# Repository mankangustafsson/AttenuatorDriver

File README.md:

# AttenuatorDriver
Attenuator switch and relay driver similar to HP11713A/B. This project covers many firsts for me: First project using KiCad, first project published on github, first Python code (GPIB control) so please bear with me.

## Hardware
The HW design started out with the solenoid control of the attenuator switches inspired by the HP 33311 product overview pdf. After a while I decided to not care about the TTL output part and just trust the LED indicators.

Each attenuator solenoid is controlled by two ULN2803 outputs. 8 attenuators in total thus requires all outputs in two ULN2803:s.

To control coaxial relays I wanted to be able to handle latching relays that is controlled by polarity switching the coil voltage. For that task I found the SN754410 Quad Half-H Driver from Texas Instruments. There are cheaper circuits that can achieve this but this is the only one I found that could handle 28V coils.

To keep the micro controller I/O pin count as low as possible I decided to control the attenuators and relays drive circuits with plain old shift registers. So three 74HC595 gets the 24 output pin count down to just four.

I also wanted to keep my options open to which kind of display I would use, so that is why both I2C and SPI connectors are available. I ended up with an LCD1602 controlled via I2C. For input I wanted to mimic the HP 11713A so I wanted 10 push buttons so two R2R ladders handles five buttons each. But I also wanted to utilize the display and I find using rotary encoders with a push button quite powerful to navigate a simple UI.

### Power Supply
This can be improved but the current design works for me. The HW is fed with 12VDC and 24VDC to the ULN2803 controlling the first four attenuators. The second set of attenuators and the relays can also be feed directly with this 24V supply. Or they can have a lower voltage controlled by their individual LM317 voltage regulator. This mean that the first attenuator group decides the highest voltage that the other atteunators and relays can use.

To remedy this I would put one extra LM317 to control the voltage to the first attenuator group and remove the J6 and J7 jumpers. This way each attenuator group and the relay pair could have their coils voltages individually set.

### Patches
I made the faulty assumption about coaxial relays could control the LED the same way the attenuators did. They do not! So the remedy is to use two free micro controller pins (I use A1 and A2) to control the relay LED indicators. Depending on LEDs used the micro controller could probably drive them directly or you could still use Q3 and Q4 to sink the current. Regardless solution you select you need to remove R4 and R6.

## Arduino Software
First of all: Do not expect any compilation support from me. You are on your own. Arduino environment is messy when it comes to how it handles libraries used. I usually import the source code of the libraries I use into the project. However since I'm not the author of the [display library] I use you have to download it yourself. The current code also includes another library, Streaming, which I only used initially in this project so remove that include statement.

Second: Parts of the code is structured and easy to read. Some parts are not structured at all and poorly documented. I'm of the opinion that code should be written to be easy to understand by other programmers and therefore would not need much documentation. It is not currently in the "easy to understand" state and it might never be.

## GPIB Control
In order to avoid the Arduino being reset every time you connect to the serial port, you need to remove the capacitor between the CH340 DTR pin and the Arduino reset pin. Note that this will make it harder to upload new software to the Arduino. You will need to push the reset button manually at the proper moment during code upload.

I've written some Python code using PyVisa to control the attenuators and relays.

[display library]:       http://www.mathertel.de/Arduino/LiquidCrystal_PCF8574.aspx

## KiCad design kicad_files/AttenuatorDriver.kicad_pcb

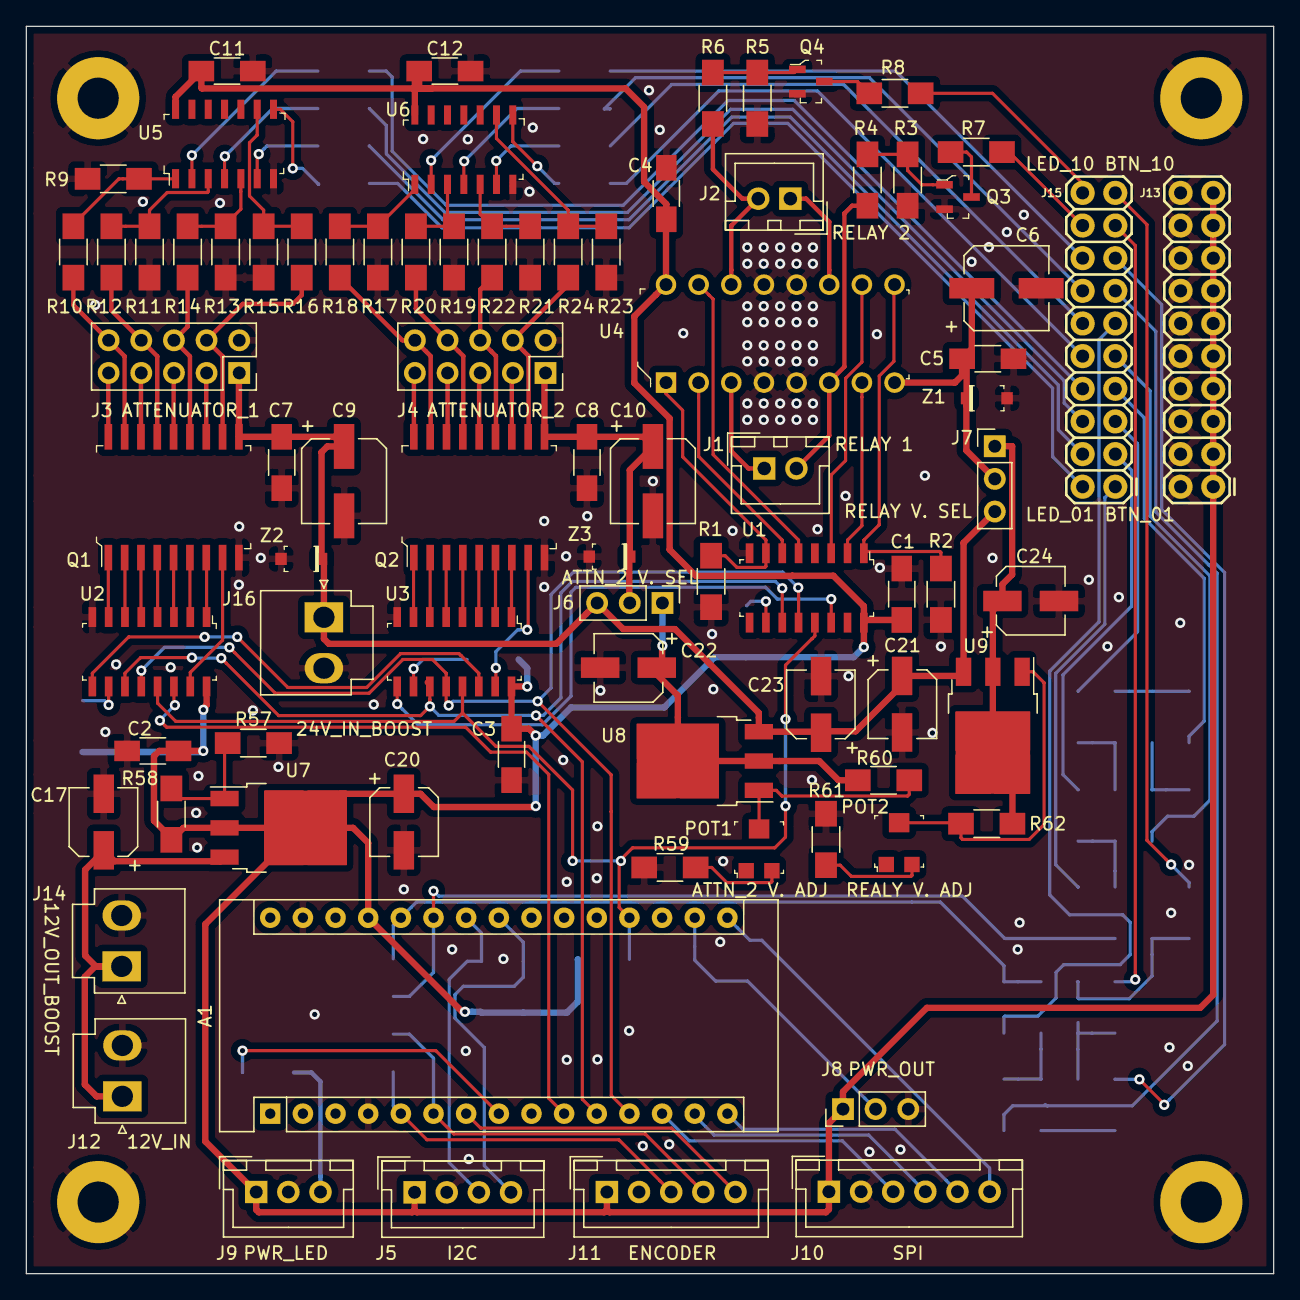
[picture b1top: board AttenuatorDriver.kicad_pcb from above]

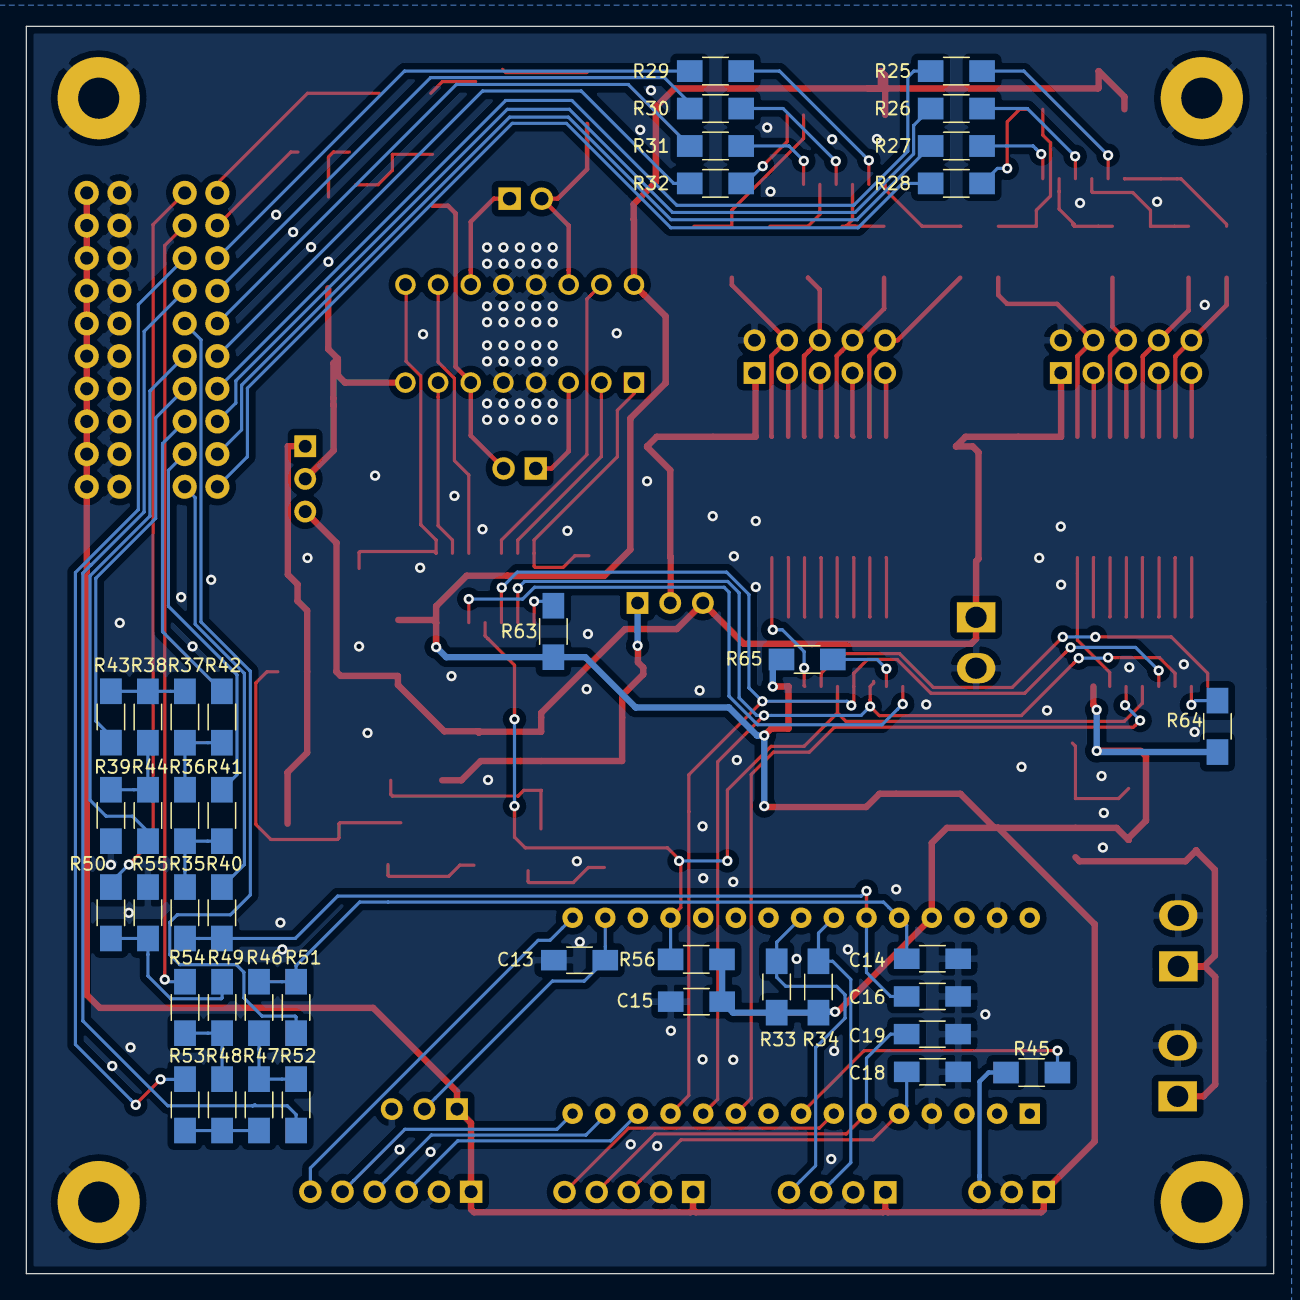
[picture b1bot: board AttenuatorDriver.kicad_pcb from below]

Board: 2 copper layers, 97.0 x 97.0 mm, 128 parts (41 on the bottom side), 126 nets.

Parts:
A1: Arduino_Nano_v3.x; Arduino_Nano
C1, C2, C3, C4, C7, C8, C11, C12, C13, C14, C15, C16, C18, C19: 0.1uF; C_1206_HandSoldering
C5: 1uF; C_1206_HandSoldering
C6, C9, C10: 47u; CP_Elec_6.3x7.7
C17, C21, C23: 1u; CP_Elec_5x5.3
C20, C22, C24: 4.7u; CP_Elec_5x5.3
H1, H2, H3, H4: MountingHole_Pad; MountingHole_3.2mm_M3_Pad
J1: RELAY_1; JST_XH_B02B-XH-A_02x2.50mm_Straight
J2: RELAY_2; JST_XH_B02B-XH-A_02x2.50mm_Straight
J3: ATTENUATOR_1; Socket_Strip_Straight_2x05_Pitch2.54mm
J4: ATTENUATOR_2; Socket_Strip_Straight_2x05_Pitch2.54mm
J5: I2C; JST_XH_B04B-XH-A_04x2.50mm_Straight
J6: DRV_PWR_SEL2; Pin_Header_Straight_1x03_Pitch2.54mm
J7: DRV_PWR_SEL3; Pin_Header_Straight_1x03_Pitch2.54mm
J8: PWR_OUT; Pin_Header_Straight_1x03_Pitch2.54mm
J9: PWR_LED; JST_XH_B03B-XH-A_03x2.50mm_Straight
J10: SPI; JST_XH_B06B-XH-A_06x2.50mm_Straight
J11: ENCODER; JST_XH_B05B-XH-A_05x2.50mm_Straight
J12: 12V_IN; JST_VH_B2P-VH-B_2x3.96mm_Vertical
J13, J15: Conn_02x10_Odd_Even; 2X10
J14: 12V_OUT_BOOST; JST_VH_B2P-VH-B_2x3.96mm_Vertical
J16: 24V_IN_BOOST; JST_VH_B2P-VH-B_2x3.96mm_Vertical
POT1, POT2: 5k; Trimpot_3.8mmx3.6mm_TC33X-2-103E
Q1, Q2: ULN2803ADWR; SOIC-18_W7.5mm
Q3, Q4: PDTC114Y; SOT-23-3
R1, R2, R4, R6, R10, R12, R14, R16, R18, R20, R22, R24, R63, R64, R65: 4.7k; R_1206_HandSoldering
R3, R5, R9, R11, R13, R15, R17, R19, R21, R23: 620; R_1206_HandSoldering
R7, R8, R25, R26, R27, R28, R29, R30, R31, R32, R58: 330; R_1206_HandSoldering
R33, R34, R56: 10k; R_1206_HandSoldering
R35, R36, R37, R38, R45, R46, R47, R48, R49, R57: 1k; R_1206_HandSoldering
R39, R40, R41, R42, R43, R44, R50, R51, R52, R53, R54, R55: 2k; R_1206_HandSoldering
R59, R61: 680; R_1206_HandSoldering
R60, R62: 240; R_1206_HandSoldering
U1, U2, U3: 74HC595; SOIC-16_W3.90mm
U4: SN754410NE; DIP-16_W7.62mm
U5, U6: SN74LS06DR; SOIC-14_W3.9mm
U7, U8, U9: V_REG_317DPACK; TO-252-3_TabPin2
Z1, Z2, Z3: MMSZ4713-TP; SOD-123

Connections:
+5V: A1.27, C1.1, C2.1, C3.1, C4.1, C11.1, C12.1, C15.2, C20.1, J5.1, J8.1, J9.1, J10.1, J11.1, J13.1, J13.3, J13.5, J13.7, J13.9, J13.11, J13.13, J13.15, J13.17, J13.19, R33.1, R34.1, R56.1, R58.1, R63.1, R64.1, R65.1, U1.16, U2.16, U3.16, U4.16, U5.14, U6.14, U7.2
+8V: C5.1, C6.1, J7.2, U4.8, Z1.K
+9V: C24.1, J7.1, R62.1, U9.2
+12V: C17.1, J12.1, J14.1, U7.3
+15V: C22.1, J6.1, R60.1, U8.2
+24V: C7.1, C9.1, C21.1, C23.1, J3.1, J6.3, J7.3, J16.1, Q1.10, U8.3, U9.3, Z2.K
+VSW: C8.1, C10.1, J4.1, J6.2, Q2.10, Z3.K
/RELAY_1A: U1.6, U4.2
/RELAY_1B: U1.2, U4.7
/RELAY_1_EN: R1.1, U1.7, U4.1
/RELAY_2A: U1.3, U4.10
/RELAY_2B: U1.5, U4.15
/RELAY_2_EN: R2.1, U1.1, U4.9
/SER_CASC_1: U2.9, U3.14
/SER_CASC_2: U1.14, U3.9
BTN_01: J15.1, R40.1
BTN_02: J15.3, R41.1
BTN_03: J15.5, R42.1
BTN_04: J15.7, R43.1
BTN_05: J15.9, R44.1
BTN_06: J15.11, R51.1
BTN_07: J15.13, R52.1
BTN_08: J15.15, R53.1
BTN_09: J15.17, R54.1
BTN_10: J15.19, R55.1
BTN_G1: A1.25, C16.2, R35.1, R40.2
BTN_G2: A1.26, C14.2, R46.1, R51.2
CE_DISP: A1.13, J10.3
ENC_BTN: A1.7, J11.5
ENC_CLK: A1.6, C19.2, J11.4
ENC_DATA: A1.5, C18.2, J11.3
GND: A1.4, A1.29, C1.2, C2.2, C3.2, C4.2, C5.2, C6.2, C7.2, C8.2, C9.2, C10.2, C11.2, C12.2, C13.1, C14.1, C15.1, C16.1, C17.2, C18.1, C19.1, C20.2, C21.2, C22.2, C23.2, C24.2, H1.1, H2.1, H3.1, H4.1, J3.2, J4.2, J5.2, J8.3, J9.2, J10.2, J11.2, J12.2, J13.2, J13.4, J13.6, J13.8, J13.10, J13.12, J13.14, J13.16, J13.18, J13.20, J14.2, J16.2, Q1.9, Q2.9, Q3.2, Q4.2, R1.2, R2.2, R3.2, R5.2, R9.2, R11.2, R13.2, R15.2, R17.2, R19.2, R21.2, R23.2, R39.2, R50.2, R57.2, R59.2, R61.2, U1.8, U2.8, U3.8, U4.4, U4.5, U4.12, U4.13, U5.7, U6.7, Z1.A, Z2.A, Z3.A
I2C_SCL: A1.24, J5.3, R34.2
I2C_SDA: A1.23, J5.4, R33.2
LED_01: J15.2, R28.1
LED_02: J15.4, R27.1
LED_03: J15.6, R26.1
LED_04: J15.8, R25.1
LED_05: J15.10, R32.1
LED_06: J15.12, R31.1
LED_07: J15.14, R30.1
LED_08: J15.16, R29.1
LED_09: J15.18, R7.1
LED_10: J15.20, R8.1
MISO: A1.15, J10.5
MOSI: A1.14, J10.4
unnamed: A1.17, C13.2, J8.2
unnamed: J1.1, U4.3
unnamed: J1.2, R4.2, U4.6
unnamed: J2.1, U4.11
unnamed: J2.2, R6.2, U4.14
unnamed: J3.3, Q1.12
unnamed: J3.4, Q1.11, R16.2
unnamed: J3.5, Q1.14
unnamed: J3.6, Q1.13, R14.2
unnamed: J3.7, Q1.16
unnamed: J3.8, Q1.15, R12.2
unnamed: J3.9, Q1.18
unnamed: J3.10, Q1.17, R10.2
unnamed: J4.3, Q2.12
unnamed: J4.4, Q2.11, R24.2
unnamed: J4.5, Q2.14
unnamed: J4.6, Q2.13, R22.2
unnamed: J4.7, Q2.16
unnamed: J4.8, Q2.15, R20.2
unnamed: J4.9, Q2.18
unnamed: J4.10, Q2.17, R18.2
unnamed: J9.3, R45.1
unnamed: POT1.2, R60.2, U8.1
unnamed: POT1.3, R59.1
unnamed: POT2.2, R62.2, U9.1
unnamed: POT2.3, R61.1
unnamed: Q1.1, U2.7
unnamed: Q1.2, U2.6
unnamed: Q1.3, U2.5
unnamed: Q1.4, U2.4
unnamed: Q1.5, U2.3
unnamed: Q1.6, U2.2
unnamed: Q1.7, U2.1
unnamed: Q1.8, U2.15
unnamed: Q2.1, U3.7
unnamed: Q2.2, U3.6
unnamed: Q2.3, U3.5
unnamed: Q2.4, U3.4
unnamed: Q2.5, U3.3
unnamed: Q2.6, U3.2
unnamed: Q2.7, U3.1
unnamed: Q2.8, U3.15
unnamed: Q3.1, R3.1, R4.1
unnamed: Q3.3, R7.2
unnamed: Q4.1, R5.1, R6.1
unnamed: Q4.3, R8.2
unnamed: R9.1, R10.1, U5.1
unnamed: R11.1, R12.1, U5.3
unnamed: R13.1, R14.1, U5.5
unnamed: R15.1, R16.1, U5.9
unnamed: R17.1, R18.1, U6.1
unnamed: R19.1, R20.1, U6.3
unnamed: R21.1, R22.1, U6.5
unnamed: R23.1, R24.1, U6.9
unnamed: R25.2, U5.2
unnamed: R26.2, U5.4
unnamed: R27.2, U5.6
unnamed: R28.2, U5.8
unnamed: R29.2, U6.2
unnamed: R30.2, U6.4
unnamed: R31.2, U6.6
unnamed: R32.2, U6.8
unnamed: R35.2, R36.1, R41.2
unnamed: R36.2, R37.1, R42.2
unnamed: R37.2, R38.1, R43.2
unnamed: R38.2, R39.1, R44.2
unnamed: R46.2, R47.1, R52.2
unnamed: R47.2, R48.1, R53.2
unnamed: R48.2, R49.1, R54.2
unnamed: R49.2, R50.1, R55.2
unnamed: R57.1, R58.2, U7.1
unnamed: R63.2, U1.10
unnamed: R64.2, U2.10
unnamed: R65.2, U3.10
PWR_LED: A1.8, R45.2
SCK: A1.16, J10.6
SER_CLK: A1.11, U1.11, U2.11, U3.11
SER_DATA: A1.10, U2.14
SER_LATCH: A1.12, U1.12, U2.12, U3.12
~SER_EN: A1.19, R56.2, U1.13, U2.13, U3.13

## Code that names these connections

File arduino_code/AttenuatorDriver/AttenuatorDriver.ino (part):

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#include "LiquidCrystal_PCF8574.h"
#include "TButton.h"

const int SER_DATA = 7;
const int SER_CLK = 8;
const int SER_LATCH = 9;
const int SER_ENABLE = A0;

const int BUTTONS_G1 = A6;
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public:
  TRelayDriver()
  {
    pinMode(SER_DATA, OUTPUT);
    pinMode(SER_CLK, OUTPUT);
    pinMode(SER_LATCH, OUTPUT);
    pinMode(SER_ENABLE, OUTPUT);
    digitalWrite(SER_ENABLE, LOW);
    Send(0x00, 0x00, 0x00, true);
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
  bool CheckRelays(uint8_t data)
  {
    if (((data & 0x01) != 0                // If RELAY_1_EN high
         && (data & 0x22) == 0x22)         // Both RELAY_1A and 1B can't be high
        || (((data & 0x40) != 0            // or if RELAY_2_EN high
             && (data & 0x14) == 0x14))) { // Both RELAY_2A and 2B can't be high
      char msg[100];
      sprintf(msg, "Invalid relay setting: 0x%02x\n", data);
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
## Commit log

2020-04-19 GPIB example code
2020-04-19 Link to display library
